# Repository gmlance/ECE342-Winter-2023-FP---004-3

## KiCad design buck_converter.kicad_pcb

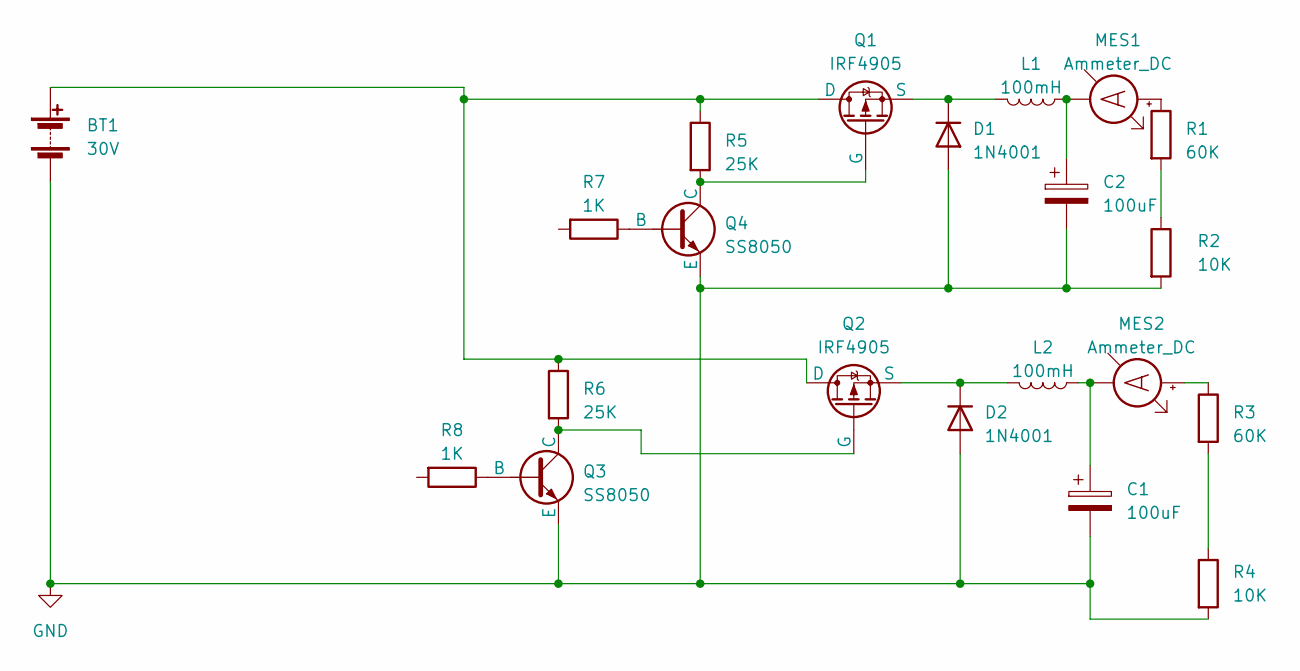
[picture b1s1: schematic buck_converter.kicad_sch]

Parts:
BT1: 30V
C1, C2: 100uF; CP_Elec_8x11.9
D1, D2: 1N4001; D_SC-80_HandSoldering
L1, L2: 100mH
MES1, MES2: Ammeter_DC
Q1, Q2: IRF4905
Q3, Q4: SS8050
R1, R3: 60K
R2, R4: 10K
R5, R6: 25K
R7, R8: 1K

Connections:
GND: BT1.2 (-), C1.2, C2.2, D1.2 (A), D2.2 (A), Q3.3 (E), Q4.3 (E), R2.2, R4.2
unnamed: BT1.1 (+), Q1.1 (D), Q2.1 (D), R5.1, R6.1
unnamed: D1.1 (K), L1.2, Q1.3 (S)
unnamed: D2.1 (K), L2.2, Q2.3 (S)
unnamed: MES1.2 (+), R1.1
unnamed: C2.1, L1.1, MES1.1 (-)
unnamed: MES2.2 (+), R3.1
unnamed: C1.1, L2.1, MES2.1 (-)
unnamed: Q1.2 (G), Q4.1 (C), R5.2
unnamed: Q2.2 (G), Q3.1 (C), R6.2
unnamed: Q3.2 (B), R8.1
unnamed: Q4.2 (B), R7.1
unnamed: R1.2, R2.1
unnamed: R3.2, R4.1

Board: 2 copper layers, 20 parts (0 on the bottom side), 14 nets, no tracks yet.

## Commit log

2023-02-03 Create Temperature Control
2023-02-03 Add SCPI input code
2023-02-04 Initial code that will be modified for LCD display
2023-02-04 LCD display code to be tested
2023-02-04 Edited with voltage range
2023-02-06 Update Temperature Control
    Bug fixes and a more final version that does not continuously print to the serial out
2023-02-07 Linear outputs and inputs to floats
2023-02-08 Update Temperature Control
    Includes wait period to see if the sensor is throwing a bogus value that should be ignored
2023-02-08 Update Temperature Control
2023-02-10 Update LCD Display
    lcd code with auto coiinter for checkoff to show the minimum maximum function
2023-02-10 LCD Display takes input, show h or l
    LCD Display receives users' input, then sees whether or not it exceeds the range. If it does, it will indicate whether it is high or low in the final display. Program will not quit, user has unlimite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
2023-02-10 LCD Display Checkoff Test Code
2023-02-13 One sensor controlling a relay
2023-02-27 Finds I2C addresses
2023-02-28 Added main code file
    Things to be added: SCPI edits, LCD code, buck converter code, temperature sensor code.
2023-03-07 Update Power_Supply_Main.ino
    updated the LCD write
2023-03-07 Update Power_Supply_Main.ino
    removed serial, implemented the dmm_out stuff
